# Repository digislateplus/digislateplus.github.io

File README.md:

# DigiSlate+

DigiSlate+ is based on the [DigiSlate](https://www.youtube.com/watch?v=TnaWQZtmPek) and is inspired by the DIY timecode generator from [mitkunz](https://github.com/mitkunz/diy_timecode_generator). The aim for the DigiSlate+ is not only to be able to read and display timecode, but also to generate it itself. To make this possible, the hardware is extended by a real time clock with high running accuracy. The RTC module DS3231 with temperature-compensated quartz offers the possibility.

There are two versions of the DigiSlate+. The simpler version is based on modified hardware from the original DigiSlate project and the software in the master branch.

The newly developed hardware offers significantly more functions. The corresponding code can be found in the dotmatrix branch.

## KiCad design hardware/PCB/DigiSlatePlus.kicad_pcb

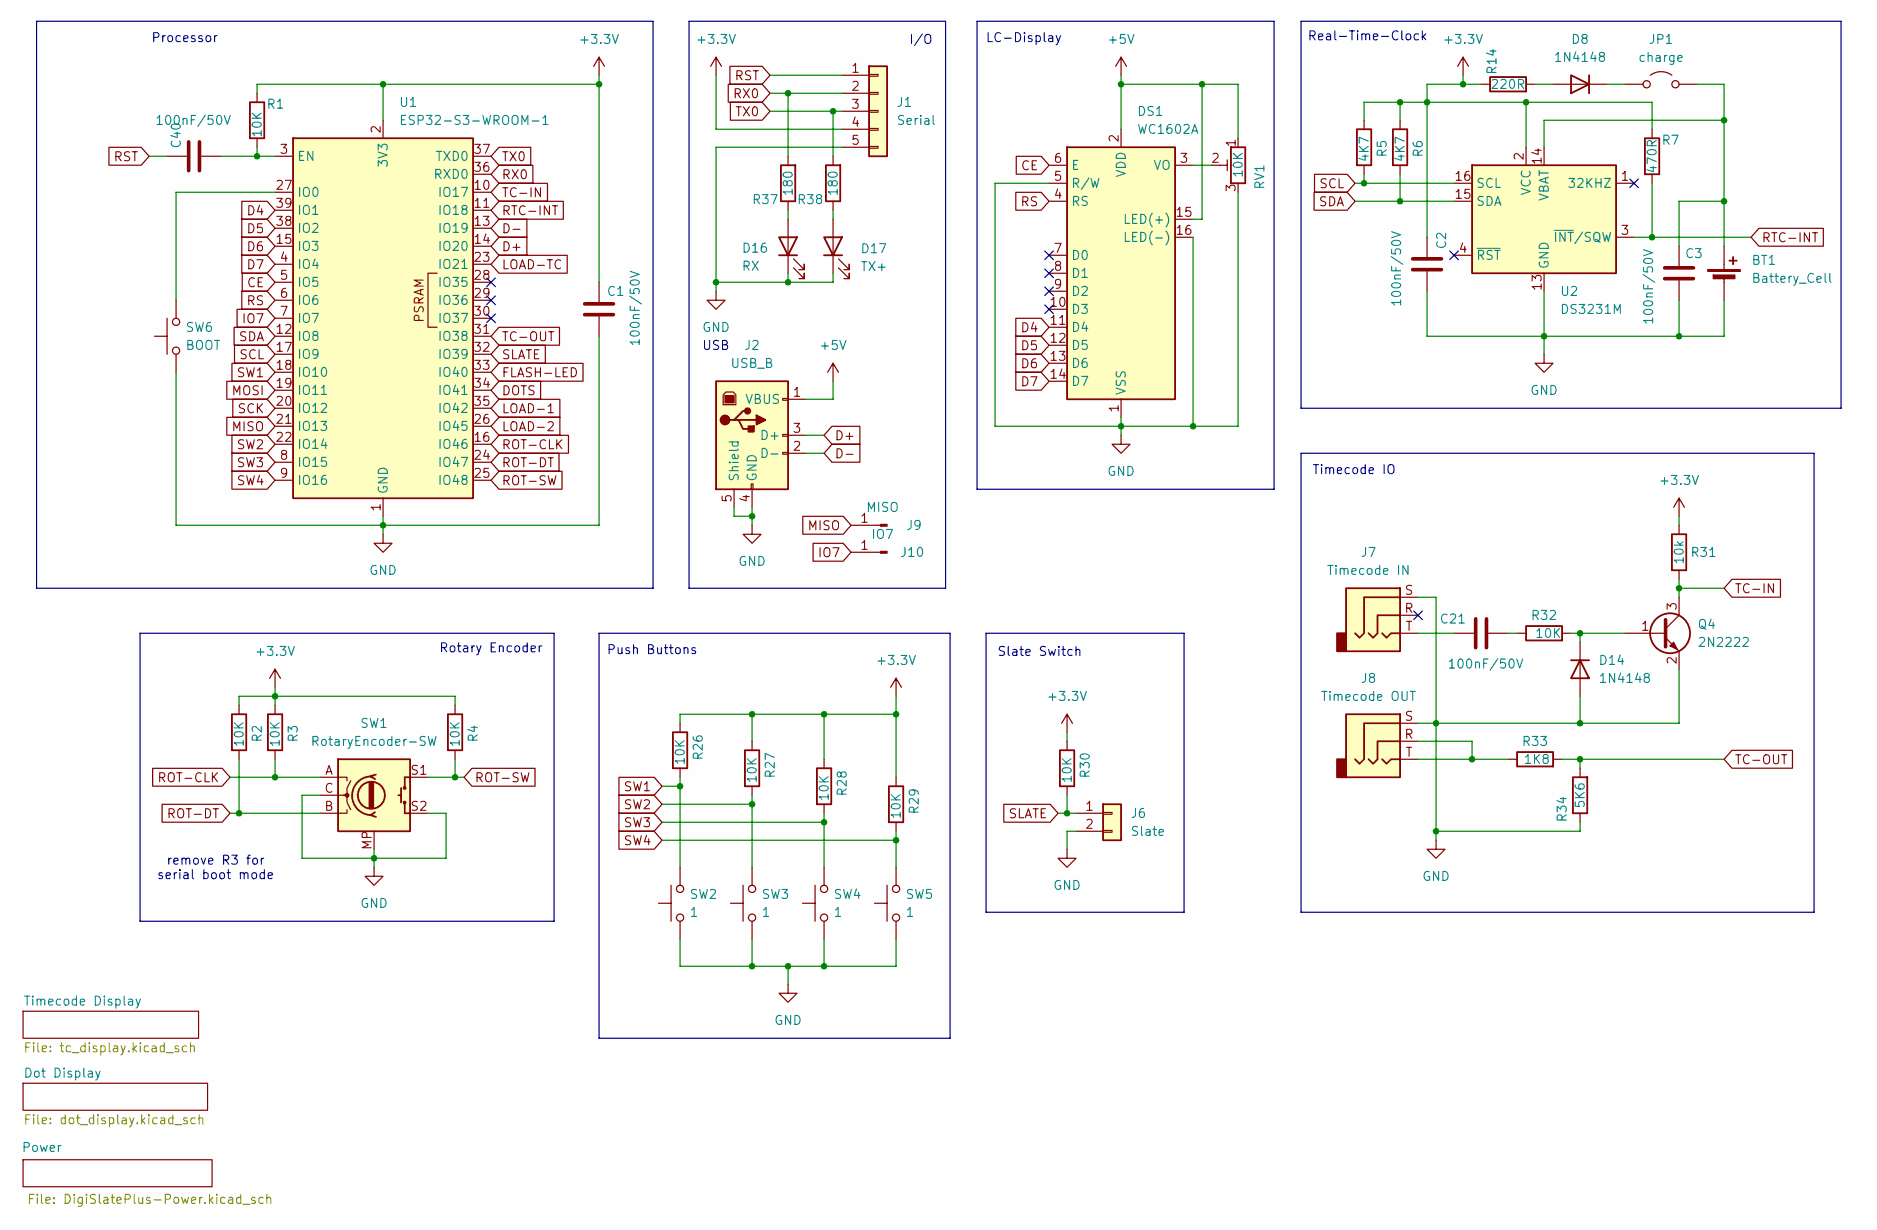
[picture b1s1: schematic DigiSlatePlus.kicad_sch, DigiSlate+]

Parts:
BT1: Battery_Cell; BatteryHolder_ComfortableElectronic_CH273-2450_1x2450
C1, C2, C3, C21, C40: 100nF/50V; C_1206_3216Metric_Pad1.33x1.80mm_HandSolder
D8, D14: 1N4148; D_PowerDI-123
D16: RX; LED_0603_1608Metric
D17: TX+; LED_0603_1608Metric
DS1: WC1602A
J1: Serial; JST_XH_B5B-XH-AM_1x05_P2.50mm_Vertical
J2: USB_B; USB_B_Lumberg_2411_02_Horizontal
J6: Slate; JST_XH_B2B-XH-AM_1x02_P2.50mm_Vertical
J7: Timecode IN; Jack_3.5mm_CUI_SJ1-3525N_Horizontal
J8: Timecode OUT; Jack_3.5mm_CUI_SJ1-3525N_Horizontal
J9: MISO; PinHeader_1x01_P1.00mm_Vertical
J10: IO7; PinHeader_1x01_P1.00mm_Vertical
JP1: charge; SolderJumper-2_P1.3mm_Open_TrianglePad1.0x1.5mm
Q4: 2N2222; SOT-23
R1, R2, R3, R4, R26, R27, R28, R29, R30, R32: 10K; R_1206_3216Metric
R5, R6: 4K7; R_1206_3216Metric
R7: 470R; R_1206_3216Metric
R14: 220R; R_1206_3216Metric
R31: 10k; R_1206_3216Metric
R33: 1K8; R_1206_3216Metric
R34: 5K6; R_1206_3216Metric
R37, R38: 180; R_0805_2012Metric_Pad1.20x1.40mm_HandSolder
RV1: 10K; Potentiometer_Vishay_TS53YL_Vertical
SW1: RotaryEncoder-SW; RotaryEncoder_Bourns_Horizontal
SW2, SW3, SW4, SW5: 1; SW_Tactile_Straight_KSA0Axx1LFTR
SW6: BOOT; SW_Push_SPST_NO_Alps_SKRK
U1: ESP32-S3-WROOM-1
U2: DS3231M; SOIC-16W_7.5x10.3mm_P1.27mm

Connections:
+3.3V: C1.1, C2.1, J1.4, R1.1, R2.1, R3.1, R4.1, R5.1, R6.1, R7.1, R14.1, R26.1, R27.1, R28.1, R29.1, R30.1, R31.1, U1.2 (3V3), U2.2 (VCC); also elsewhere on the board
+5V: DS1.2 (VDD), DS1.15 (LED(+)), J2.1 (VBUS), RV1.1; also elsewhere on the board
CE: DS1.6 (E), U1.5 (IO5)
D4: DS1.11 (D4), U1.39 (IO1)
D5: DS1.12 (D5), U1.38 (IO2)
D6: DS1.13 (D6), U1.15 (IO3)
D7: DS1.14 (D7), U1.4 (IO4)
D+: J2.3 (D+), U1.14 (IO20)
D-: J2.2 (D-), U1.13 (IO19)
DOTS: U1.34 (IO41); also elsewhere on the board
FLASH-LED: U1.33 (IO40); also elsewhere on the board
GND: BT1.2 (-), C1.2, C2.2, C3.2, D14.2 (A), D16.1 (K), D17.1 (K), DS1.1 (VSS), DS1.5 (R/W), DS1.16 (LED(-)), J1.5, J2.4 (GND), J2.5 (Shield), J6.2, J7.S, J8.S, Q4.2 (E), R34.1, RV1.3, SW1.C, SW1.MP, SW1.S2, SW2.1, SW3.1, SW4.1, SW5.1, SW6.1, U1.1 (GND), U1.40 (GND), U1.41 (GND), U2.5 (GND), U2.6 (GND), U2.7 (GND), U2.8 (GND), U2.9 (GND), U2.10 (GND), U2.11 (GND), U2.12 (GND), U2.13 (GND); also elsewhere on the board
IO7: J10.1, U1.7 (IO7)
LOAD-1: U1.35 (IO42); also elsewhere on the board
LOAD-2: U1.26 (IO45); also elsewhere on the board
LOAD-TC: U1.23 (IO21); also elsewhere on the board
MISO: J9.1, U1.21 (IO13)
MOSI: U1.19 (IO11); also elsewhere on the board
unnamed: BT1.1 (+), C3.1, JP1.2 (B), U2.14 (VBAT)
unnamed: C21.1, J7.T
unnamed: C21.2, R32.1
unnamed: D8.2 (A), R14.2
unnamed: D8.1 (K), JP1.1 (A)
unnamed: D14.1 (K), Q4.1 (B), R32.2
unnamed: D16.2 (A), R37.1
unnamed: D17.2 (A), R38.1
unnamed: DS1.3 (VO), RV1.2
unnamed: J8.R, J8.T, R33.1
unnamed: C40.2, R1.2, U1.3 (EN)
unnamed: SW6.2, U1.27 (IO0)
ROT-CLK: R3.2, SW1.A, U1.16 (IO46)
ROT-DT: R2.2, SW1.B, U1.24 (IO47)
ROT-SW: R4.2, SW1.S1, U1.25 (IO48)
RS: DS1.4 (RS), U1.6 (IO6)
RST: C40.1, J1.1
RTC-INT: R7.2, U1.11 (IO18), U2.3 (~INT/SQW)
RX0: J1.2, R37.2, U1.36 (RXD0)
SCK: U1.20 (IO12); also elsewhere on the board
SCL: R5.2, U1.17 (IO9), U2.16 (SCL)
SDA: R6.2, U1.12 (IO8), U2.15 (SDA)
SLATE: J6.1, R30.2, U1.32 (IO39)
SW1: R26.2, SW2.2, U1.18 (IO10)
SW2: R27.2, SW3.2, U1.22 (IO14)
SW3: R28.2, SW4.2, U1.8 (IO15)
SW4: R29.2, SW5.2, U1.9 (IO16)
TC-IN: Q4.3 (C), R31.2, U1.10 (IO17)
TC-OUT: R33.2, R34.2, U1.31 (IO38)
TX0: J1.3, R38.2, U1.37 (TXD0)

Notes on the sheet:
Real-Time-Clock
Push Buttons
Timecode IO
remove R3 for serial boot mode
I/O
USB
Rotary Encoder
Slate Switch
LC-Display
Processor

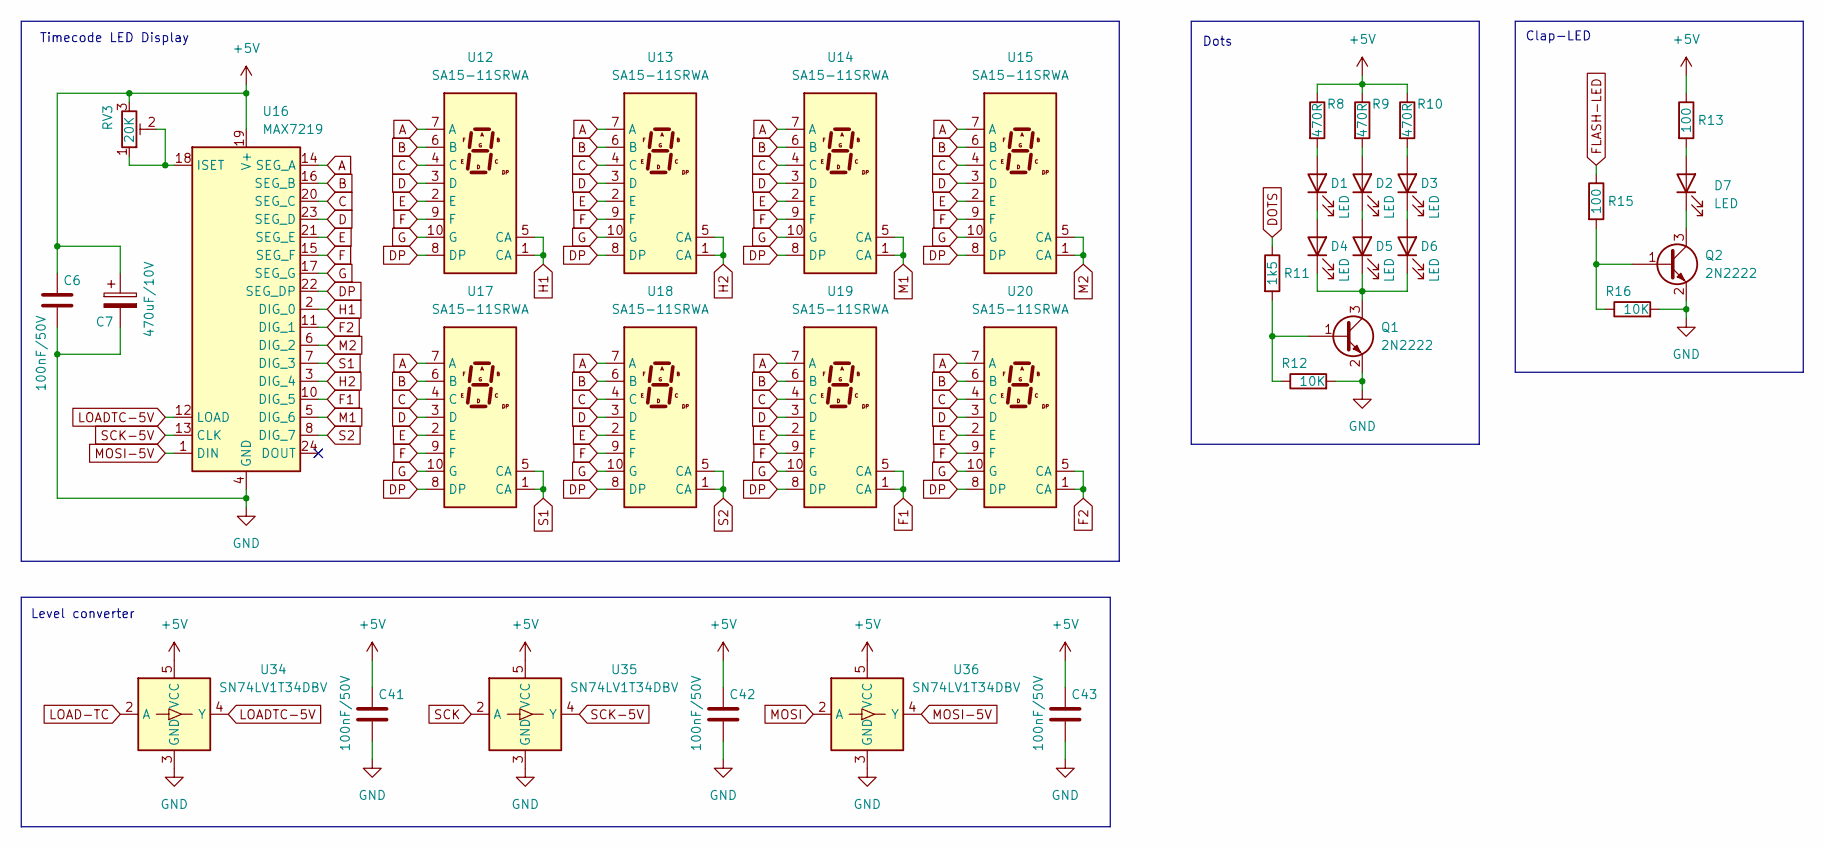
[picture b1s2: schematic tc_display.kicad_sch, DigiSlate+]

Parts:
C6, C41, C42, C43: 100nF/50V; C_1206_3216Metric_Pad1.33x1.80mm_HandSolder
C7: 470uF/10V; CP_EIA-7343-31_Kemet-D_Pad2.25x2.55mm_HandSolder
D1, D2, D3, D4, D5, D6: LED; LED_D3.0mm_FlatTop
D7: LED; LED_D10.0mm
Q1, Q2: 2N2222; SOT-23
R8, R9, R10: 470R; R_1206_3216Metric
R11: 1k5; R_1206_3216Metric
R12, R16: 10K; R_1206_3216Metric
R13, R15: 100; R_1206_3216Metric
RV3: 20K; Potentiometer_Vishay_TS53YL_Vertical
U12, U13, U14, U15, U17, U18, U19, U20: SA15-11SRWA; FYS-12011A
U16: MAX7219; SOIC-24W_7.5x15.4mm_P1.27mm
U34, U35, U36: SN74LV1T34DBV; SOT-23-5

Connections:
+5V: C6.1, C7.1, C41.1, C42.1, C43.1, R8.1, R9.1, R10.1, R13.1, RV3.3, U16.19 (V+), U34.5 (VCC), U35.5 (VCC), U36.5 (VCC); also elsewhere on the board
A: U12.7 (A), U13.7 (A), U14.7 (A), U15.7 (A), U16.14 (SEG_A), U17.7 (A), U18.7 (A), U19.7 (A), U20.7 (A)
B: U12.6 (B), U13.6 (B), U14.6 (B), U15.6 (B), U16.16 (SEG_B), U17.6 (B), U18.6 (B), U19.6 (B), U20.6 (B)
C: U12.4 (C), U13.4 (C), U14.4 (C), U15.4 (C), U16.20 (SEG_C), U17.4 (C), U18.4 (C), U19.4 (C), U20.4 (C)
D: U12.3 (D), U13.3 (D), U14.3 (D), U15.3 (D), U16.23 (SEG_D), U17.3 (D), U18.3 (D), U19.3 (D), U20.3 (D)
DOTS: R11.1; also elsewhere on the board
DP: U12.8 (DP), U13.8 (DP), U14.8 (DP), U15.8 (DP), U16.22 (SEG_DP), U17.8 (DP), U18.8 (DP), U19.8 (DP), U20.8 (DP)
E: U12.2 (E), U13.2 (E), U14.2 (E), U15.2 (E), U16.21 (SEG_E), U17.2 (E), U18.2 (E), U19.2 (E), U20.2 (E)
F: U12.9 (F), U13.9 (F), U14.9 (F), U15.9 (F), U16.15 (SEG_F), U17.9 (F), U18.9 (F), U19.9 (F), U20.9 (F)
F1: U16.10 (DIG_5), U19.1 (CA), U19.5 (CA)
F2: U16.11 (DIG_1), U20.1 (CA), U20.5 (CA)
FLASH-LED: R15.1; also elsewhere on the board
G: U12.10 (G), U13.10 (G), U14.10 (G), U15.10 (G), U16.17 (SEG_G), U17.10 (G), U18.10 (G), U19.10 (G), U20.10 (G)
GND: C6.2, C7.2, C41.2, C42.2, C43.2, Q1.2 (E), Q2.2 (E), R12.2, R16.2, U16.4 (GND), U16.9 (GND), U34.3 (GND), U35.3 (GND), U36.3 (GND); also elsewhere on the board
H1: U12.1 (CA), U12.5 (CA), U16.2 (DIG_0)
H2: U13.1 (CA), U13.5 (CA), U16.3 (DIG_4)
LOAD-TC: U34.2 (A); also elsewhere on the board
LOADTC-5V: U16.12 (LOAD), U34.4 (Y)
M1: U14.1 (CA), U14.5 (CA), U16.5 (DIG_6)
M2: U15.1 (CA), U15.5 (CA), U16.6 (DIG_2)
MOSI: U36.2 (A); also elsewhere on the board
MOSI-5V: U16.1 (DIN), U36.4 (Y); also elsewhere on the board
unnamed: D1.2 (A), R8.2
unnamed: D1.1 (K), D4.2 (A)
unnamed: D2.2 (A), R9.2
unnamed: D2.1 (K), D5.2 (A)
unnamed: D3.2 (A), R10.2
unnamed: D3.1 (K), D6.2 (A)
unnamed: D4.1 (K), D5.1 (K), D6.1 (K), Q1.3 (C)
unnamed: D7.2 (A), R13.2
unnamed: D7.1 (K), Q2.3 (C)
unnamed: Q1.1 (B), R11.2, R12.1
unnamed: Q2.1 (B), R15.2, R16.1
unnamed: RV3.1, RV3.2, U16.18 (ISET)
S1: U16.7 (DIG_3), U17.1 (CA), U17.5 (CA)
S2: U16.8 (DIG_7), U18.1 (CA), U18.5 (CA)
SCK: U35.2 (A); also elsewhere on the board
SCK-5V: U16.13 (CLK), U35.4 (Y); also elsewhere on the board

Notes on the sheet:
Timecode LED Display
Dots
Level converter
Clap-LED

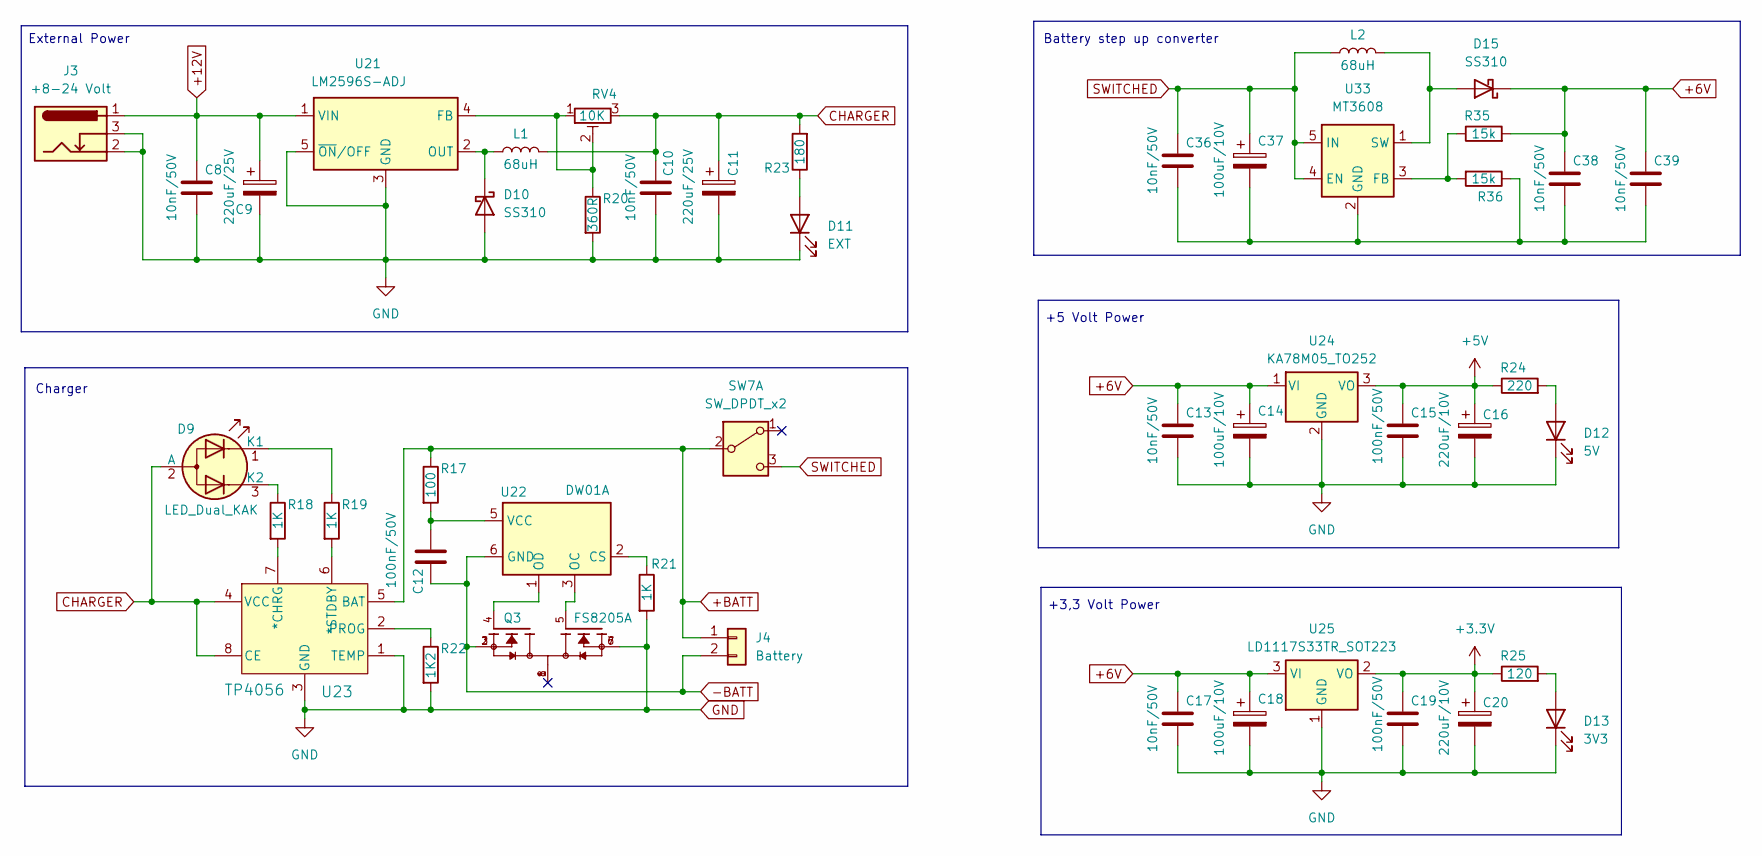
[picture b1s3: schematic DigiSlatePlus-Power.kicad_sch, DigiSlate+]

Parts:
C8, C10, C13, C17, C36, C38: 10nF/50V; C_1206_3216Metric_Pad1.33x1.80mm_HandSolder
C9, C11: 220uF/25V; CP_EIA-7343-31_Kemet-D_Pad2.25x2.55mm_HandSolder
C12, C15, C19: 100nF/50V; C_1206_3216Metric_Pad1.33x1.80mm_HandSolder
C14, C18, C37: 100uF/10V; CP_EIA-7343-31_Kemet-D_Pad2.25x2.55mm_HandSolder
C16, C20: 220uF/10V; CP_EIA-7343-31_Kemet-D_Pad2.25x2.55mm_HandSolder
C39: 10nF/50V; C_0805_2012Metric_Pad1.18x1.45mm_HandSolder
D9: LED_Dual_KAK; LED_D3.0mm-3
D10, D15: SS310; D_SMA
D11: EXT; LED_D3.0mm
D12: 5V; LED_0603_1608Metric
D13: 3V3; LED_0603_1608Metric
J3: +8-24 Volt; DC_Power_Jack_PCB_Mounted_2.1mm
J4: Battery; JST_XH_B2B-XH-AM_1x02_P2.50mm_Vertical
L1, L2: 68uH; L_7.3x7.3_H3.5
Q3: FS8205A; TSSOP-8_3x3mm_P0.65mm; PARTREV 1.7
R17: 100; R_1206_3216Metric
R18, R19, R21: 1K; R_0805_2012Metric_Pad1.20x1.40mm_HandSolder
R20: 360R; R_1206_3216Metric
R22: 1K2; R_0805_2012Metric_Pad1.20x1.40mm_HandSolder
R23: 180; R_0805_2012Metric_Pad1.20x1.40mm_HandSolder
R24: 220; R_0805_2012Metric_Pad1.20x1.40mm_HandSolder
R25: 120; R_0805_2012Metric_Pad1.20x1.40mm_HandSolder
R35, R36: 15k; R_0805_2012Metric_Pad1.20x1.40mm_HandSolder
RV4: 10K; Potentiometer_Bourns_3296W_Vertical
SW7: SW_DPDT_x2; SW_Slide_SPDT_Angled_CK_OS102011MA1Q
U21: LM2596S-ADJ; TO-263-5_TabPin3
U22: DW01A; SOT-23-6
U23: TP4056; TP4056-42-SOP8_TPW_1
U24: KA78M05_TO252; TO-252-2
U25: LD1117S33TR_SOT223; SOT-223-3_TabPin2
U33: MT3608; SOT-23-6

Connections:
+3.3V: C19.1, C20.1, R25.1, U25.2 (VO); also elsewhere on the board
+5V: C15.1, C16.1, R24.1, U24.3 (VO); also elsewhere on the board
+6V: C13.1, C14.1, C17.1, C18.1, C38.1, C39.1, D15.1 (K), R35.2, U24.1 (VI), U25.3 (VI)
+12V: C8.1, C9.1, J3.1, U21.1 (VIN)
+BATT: J4.1, R17.1, SW7.2 (B), U23.5 (BAT)
-BATT: C12.1, J4.2, Q3.2, Q3.3, U22.6 (GND)
CHARGER: C10.1, C11.1, D9.2 (A), L1.2, R23.2, RV4.3, U23.4 (VCC), U23.8 (CE)
GND: C8.2, C9.2, C10.2, C11.2, C13.2, C14.2, C15.2, C16.2, C17.2, C18.2, C19.2, C20.2, D10.2 (A), D11.1 (K), D12.1 (K), D13.1 (K), J3.2, J3.3, Q3.6, Q3.7, R20.2, R21.2, R22.2, U21.3 (GND), U21.5 (~ON/OFF), U23.1 (TEMP), U23.3 (GND), U24.2 (GND), U25.1 (GND); also elsewhere on the board
unnamed: D9.1 (K1), R19.1
unnamed: D9.3 (K2), R18.1
unnamed: D10.1 (K), L1.1, U21.2 (OUT)
unnamed: D11.2 (A), R23.1
unnamed: D12.2 (A), R24.2
unnamed: D13.2 (A), R25.2
unnamed: D15.2 (A), L2.2, U33.1 (SW)
unnamed: R20.1, RV4.1, RV4.2, U21.4 (FB)
unnamed: R21.1, U22.2 (CS)
unnamed: Q3.5, U22.3 (OC)
unnamed: Q3.4, U22.1 (OD)
unnamed: C12.2, R17.2, U22.5 (VCC)
unnamed: R18.2, U23.7 (*CHRG)
unnamed: R19.2, U23.6 (*STDBY)
unnamed: R22.1, U23.2 (PROG)
unnamed: R35.1, R36.2, U33.3 (FB)
unnamed: C36.2, C37.2, C38.2, C39.2, R36.1, U33.2 (GND)
SWITCHED: C36.1, C37.1, L2.1, SW7.3 (C), U33.4 (EN), U33.5 (IN)

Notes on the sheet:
+3,3 Volt Power
+5 Volt Power
Battery step up converter
External Power
Charger

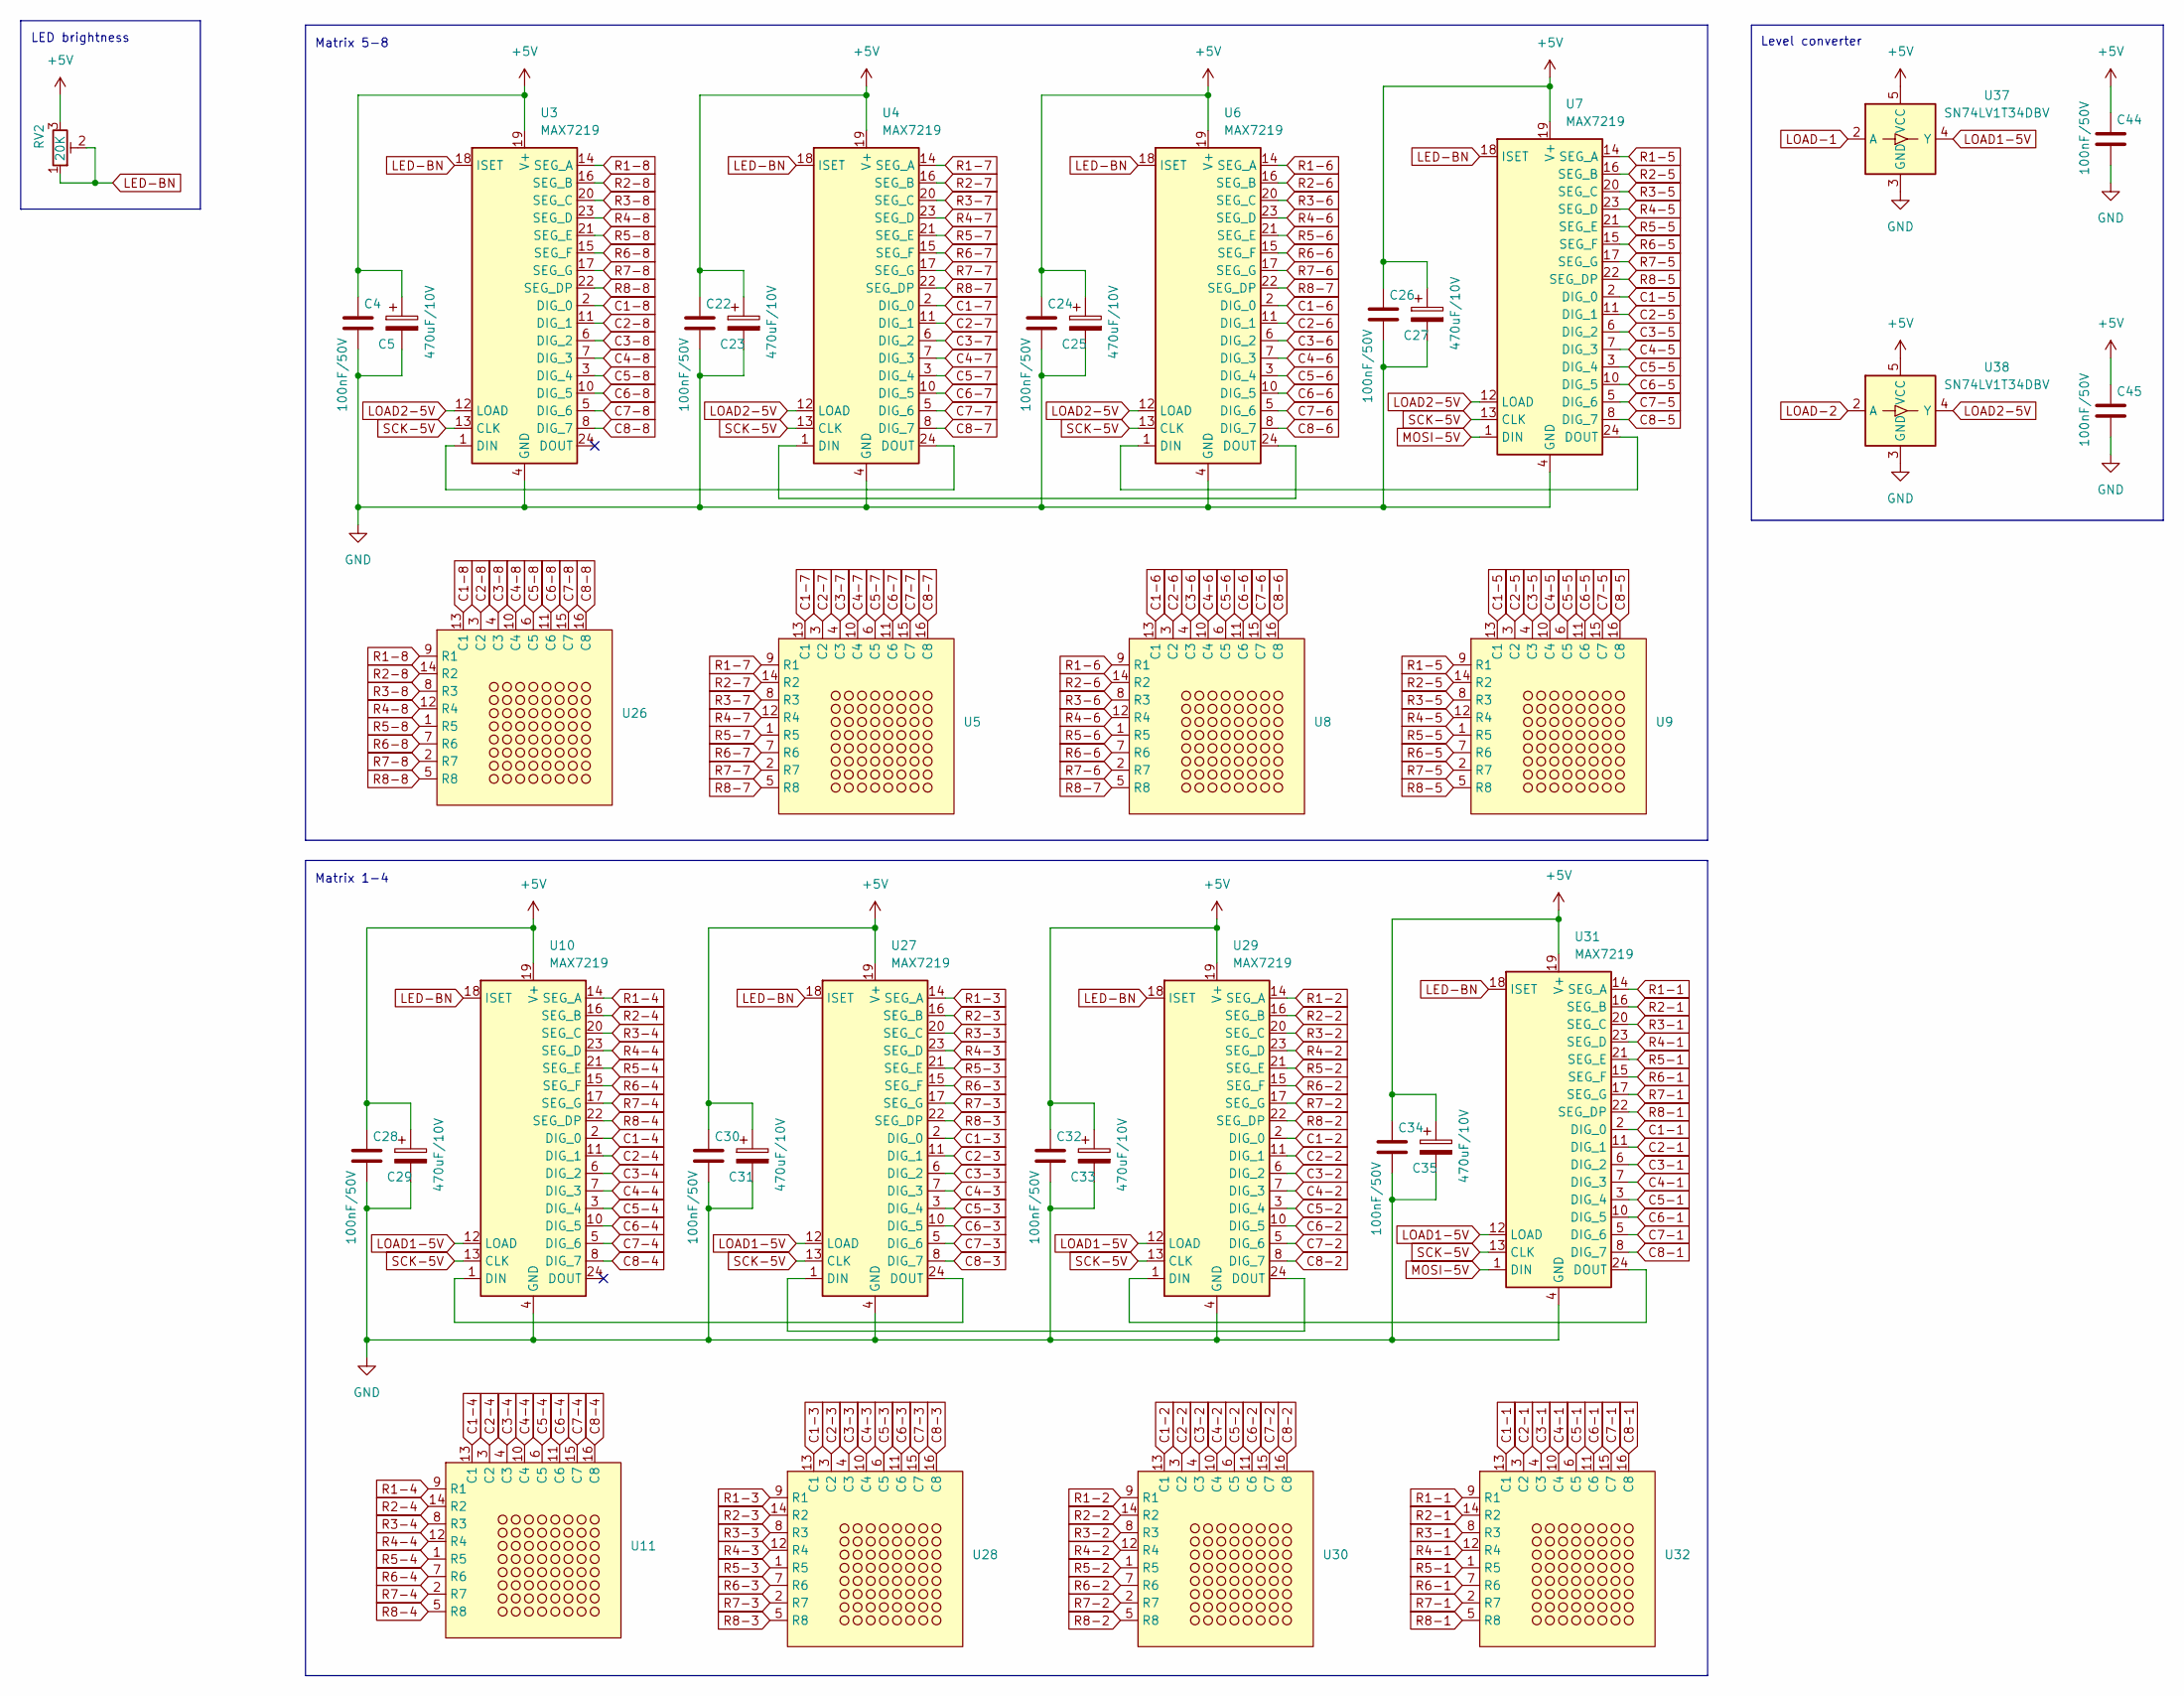
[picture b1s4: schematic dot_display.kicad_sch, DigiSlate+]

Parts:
C4, C22, C24, C26, C28, C30, C32, C34, C44, C45: 100nF/50V; C_1206_3216Metric_Pad1.33x1.80mm_HandSolder
C5, C23, C25, C27, C29, C31, C33, C35: 470uF/10V; CP_EIA-7343-31_Kemet-D_Pad2.25x2.55mm_HandSolder
RV2: 20K; Potentiometer_Vishay_TS53YL_Vertical
U3, U4, U6, U7, U10, U27, U29, U31: MAX7219; SOIC-24W_7.5x15.4mm_P1.27mm
U5, U8, U9, U11, U26, U28, U30, U32: FMY-12883
U37, U38: SN74LV1T34DBV; SOT-23-5

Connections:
+5V: C4.1, C5.1, C22.1, C23.1, C24.1, C25.1, C26.1, C27.1, C28.1, C29.1, C30.1, C31.1, C32.1, C33.1, C34.1, C35.1, C44.1, C45.1, RV2.3, U3.19 (V+), U4.19 (V+), U6.19 (V+), U7.19 (V+), U10.19 (V+), U27.19 (V+), U29.19 (V+), U31.19 (V+), U37.5 (VCC), U38.5 (VCC); also elsewhere on the board
C1-1: U31.2 (DIG_0), U32.13 (C1)
C1-2: U29.2 (DIG_0), U30.13 (C1)
C1-3: U27.2 (DIG_0), U28.13 (C1)
C1-4: U10.2 (DIG_0), U11.13 (C1)
C1-5: U7.2 (DIG_0), U9.13 (C1)
C1-6: U6.2 (DIG_0), U8.13 (C1)
C1-7: U4.2 (DIG_0), U5.13 (C1)
C1-8: U3.2 (DIG_0), U26.13 (C1)
C2-1: U31.11 (DIG_1), U32.3 (C2)
C2-2: U29.11 (DIG_1), U30.3 (C2)
C2-3: U27.11 (DIG_1), U28.3 (C2)
C2-4: U10.11 (DIG_1), U11.3 (C2)
C2-5: U7.11 (DIG_1), U9.3 (C2)
C2-6: U6.11 (DIG_1), U8.3 (C2)
C2-7: U4.11 (DIG_1), U5.3 (C2)
C2-8: U3.11 (DIG_1), U26.3 (C2)
C3-1: U31.6 (DIG_2), U32.4 (C3)
C3-2: U29.6 (DIG_2), U30.4 (C3)
C3-3: U27.6 (DIG_2), U28.4 (C3)
C3-4: U10.6 (DIG_2), U11.4 (C3)
C3-5: U7.6 (DIG_2), U9.4 (C3)
C3-6: U6.6 (DIG_2), U8.4 (C3)
C3-7: U4.6 (DIG_2), U5.4 (C3)
C3-8: U3.6 (DIG_2), U26.4 (C3)
C4-1: U31.7 (DIG_3), U32.10 (C4)
C4-2: U29.7 (DIG_3), U30.10 (C4)
C4-3: U27.7 (DIG_3), U28.10 (C4)
C4-4: U10.7 (DIG_3), U11.10 (C4)
C4-5: U7.7 (DIG_3), U9.10 (C4)
C4-6: U6.7 (DIG_3), U8.10 (C4)
C4-7: U4.7 (DIG_3), U5.10 (C4)
C4-8: U3.7 (DIG_3), U26.10 (C4)
C5-1: U31.3 (DIG_4), U32.6 (C5)
C5-2: U29.3 (DIG_4), U30.6 (C5)
C5-3: U27.3 (DIG_4), U28.6 (C5)
C5-4: U10.3 (DIG_4), U11.6 (C5)
C5-5: U7.3 (DIG_4), U9.6 (C5)
C5-6: U6.3 (DIG_4), U8.6 (C5)
C5-7: U4.3 (DIG_4), U5.6 (C5)
C5-8: U3.3 (DIG_4), U26.6 (C5)
C6-1: U31.10 (DIG_5), U32.11 (C6)
C6-2: U29.10 (DIG_5), U30.11 (C6)
C6-3: U27.10 (DIG_5), U28.11 (C6)
C6-4: U10.10 (DIG_5), U11.11 (C6)
C6-5: U7.10 (DIG_5), U9.11 (C6)
C6-6: U6.10 (DIG_5), U8.11 (C6)
C6-7: U4.10 (DIG_5), U5.11 (C6)
C6-8: U3.10 (DIG_5), U26.11 (C6)
C7-1: U31.5 (DIG_6), U32.15 (C7)
C7-2: U29.5 (DIG_6), U30.15 (C7)
C7-3: U27.5 (DIG_6), U28.15 (C7)
C7-4: U10.5 (DIG_6), U11.15 (C7)
C7-5: U7.5 (DIG_6), U9.15 (C7)
C7-6: U6.5 (DIG_6), U8.15 (C7)
C7-7: U4.5 (DIG_6), U5.15 (C7)
C7-8: U3.5 (DIG_6), U26.15 (C7)
C8-1: U31.8 (DIG_7), U32.16 (C8)
C8-2: U29.8 (DIG_7), U30.16 (C8)
C8-3: U27.8 (DIG_7), U28.16 (C8)
C8-4: U10.8 (DIG_7), U11.16 (C8)
C8-5: U7.8 (DIG_7), U9.16 (C8)
C8-6: U6.8 (DIG_7), U8.16 (C8)
C8-7: U4.8 (DIG_7), U5.16 (C8)
C8-8: U3.8 (DIG_7), U26.16 (C8)
GND: C4.2, C5.2, C22.2, C23.2, C24.2, C25.2, C26.2, C27.2, C28.2, C29.2, C30.2, C31.2, C32.2, C33.2, C34.2, C35.2, C44.2, C45.2, U3.4 (GND), U3.9 (GND), U4.4 (GND), U4.9 (GND), U6.4 (GND), U6.9 (GND), U7.4 (GND), U7.9 (GND), U10.4 (GND), U10.9 (GND), U27.4 (GND), U27.9 (GND), U29.4 (GND), U29.9 (GND), U31.4 (GND), U31.9 (GND), U37.3 (GND), U38.3 (GND); also elsewhere on the board
LED-BN: RV2.1, RV2.2, U3.18 (ISET), U4.18 (ISET), U6.18 (ISET), U7.18 (ISET), U10.18 (ISET), U27.18 (ISET), U29.18 (ISET), U31.18 (ISET)
LOAD1-5V: U10.12 (LOAD), U27.12 (LOAD), U29.12 (LOAD), U31.12 (LOAD), U37.4 (Y)
LOAD2-5V: U3.12 (LOAD), U4.12 (LOAD), U6.12 (LOAD), U7.12 (LOAD), U38.4 (Y)
LOAD-1: U37.2 (A); also elsewhere on the board
LOAD-2: U38.2 (A); also elsewhere on the board
MOSI-5V: U7.1 (DIN), U31.1 (DIN); also elsewhere on the board
unnamed: U3.1 (DIN), U4.24 (DOUT)
unnamed: U4.1 (DIN), U6.24 (DOUT)
unnamed: U6.1 (DIN), U7.24 (DOUT)
unnamed: U10.1 (DIN), U27.24 (DOUT)
unnamed: U27.1 (DIN), U29.24 (DOUT)
unnamed: U29.1 (DIN), U31.24 (DOUT)
R1-1: U31.14 (SEG_A), U32.9 (R1)
R1-2: U29.14 (SEG_A), U30.9 (R1)
R1-3: U27.14 (SEG_A), U28.9 (R1)
R1-4: U10.14 (SEG_A), U11.9 (R1)
R1-5: U7.14 (SEG_A), U9.9 (R1)
R1-6: U6.14 (SEG_A), U8.9 (R1)
R1-7: U4.14 (SEG_A), U5.9 (R1)
R1-8: U3.14 (SEG_A), U26.9 (R1)
R2-1: U31.16 (SEG_B), U32.14 (R2)
R2-2: U29.16 (SEG_B), U30.14 (R2)
R2-3: U27.16 (SEG_B), U28.14 (R2)
R2-4: U10.16 (SEG_B), U11.14 (R2)
R2-5: U7.16 (SEG_B), U9.14 (R2)
R2-6: U6.16 (SEG_B), U8.14 (R2)
R2-7: U4.16 (SEG_B), U5.14 (R2)
R2-8: U3.16 (SEG_B), U26.14 (R2)
R3-1: U31.20 (SEG_C), U32.8 (R3)
R3-2: U29.20 (SEG_C), U30.8 (R3)
R3-3: U27.20 (SEG_C), U28.8 (R3)
R3-4: U10.20 (SEG_C), U11.8 (R3)
R3-5: U7.20 (SEG_C), U9.8 (R3)
R3-6: U6.20 (SEG_C), U8.8 (R3)
R3-7: U4.20 (SEG_C), U5.8 (R3)
R3-8: U3.20 (SEG_C), U26.8 (R3)
R4-1: U31.23 (SEG_D), U32.12 (R4)
R4-2: U29.23 (SEG_D), U30.12 (R4)
R4-3: U27.23 (SEG_D), U28.12 (R4)
R4-4: U10.23 (SEG_D), U11.12 (R4)
R4-5: U7.23 (SEG_D), U9.12 (R4)
R4-6: U6.23 (SEG_D), U8.12 (R4)
R4-7: U4.23 (SEG_D), U5.12 (R4)
R4-8: U3.23 (SEG_D), U26.12 (R4)
R5-1: U31.21 (SEG_E), U32.1 (R5)
R5-2: U29.21 (SEG_E), U30.1 (R5)
R5-3: U27.21 (SEG_E), U28.1 (R5)
R5-4: U10.21 (SEG_E), U11.1 (R5)
R5-5: U7.21 (SEG_E), U9.1 (R5)
R5-6: U6.21 (SEG_E), U8.1 (R5)
R5-7: U4.21 (SEG_E), U5.1 (R5)
R5-8: U3.21 (SEG_E), U26.1 (R5)
R6-1: U31.15 (SEG_F), U32.7 (R6)
R6-2: U29.15 (SEG_F), U30.7 (R6)
R6-3: U27.15 (SEG_F), U28.7 (R6)
R6-4: U10.15 (SEG_F), U11.7 (R6)
R6-5: U7.15 (SEG_F), U9.7 (R6)
R6-6: U6.15 (SEG_F), U8.7 (R6)
R6-7: U4.15 (SEG_F), U5.7 (R6)
R6-8: U3.15 (SEG_F), U26.7 (R6)
R7-1: U31.17 (SEG_G), U32.2 (R7)
R7-2: U29.17 (SEG_G), U30.2 (R7)
R7-3: U27.17 (SEG_G), U28.2 (R7)
R7-4: U10.17 (SEG_G), U11.2 (R7)
R7-5: U7.17 (SEG_G), U9.2 (R7)
R7-6: U6.17 (SEG_G), U8.2 (R7)
R7-7: U4.17 (SEG_G), U5.2 (R7)
R7-8: U3.17 (SEG_G), U26.2 (R7)
R8-1: U31.22 (SEG_DP), U32.5 (R8)
R8-2: U29.22 (SEG_DP), U30.5 (R8)
R8-3: U27.22 (SEG_DP), U28.5 (R8)
R8-4: U10.22 (SEG_DP), U11.5 (R8)
R8-5: U7.22 (SEG_DP), U9.5 (R8)
R8-7: U4.22 (SEG_DP), U5.5 (R8), U6.22 (SEG_DP), U8.5 (R8)
R8-8: U3.22 (SEG_DP), U26.5 (R8)
SCK-5V: U3.13 (CLK), U4.13 (CLK), U6.13 (CLK), U7.13 (CLK), U10.13 (CLK), U27.13 (CLK), U29.13 (CLK), U31.13 (CLK); also elsewhere on the board

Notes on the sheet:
Level converter
LED brightness
Matrix 5-8
Matrix 1-4
